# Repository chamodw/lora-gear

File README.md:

# lora-gear
Prototype application PCB for LoRA gear wearable activity tracker.

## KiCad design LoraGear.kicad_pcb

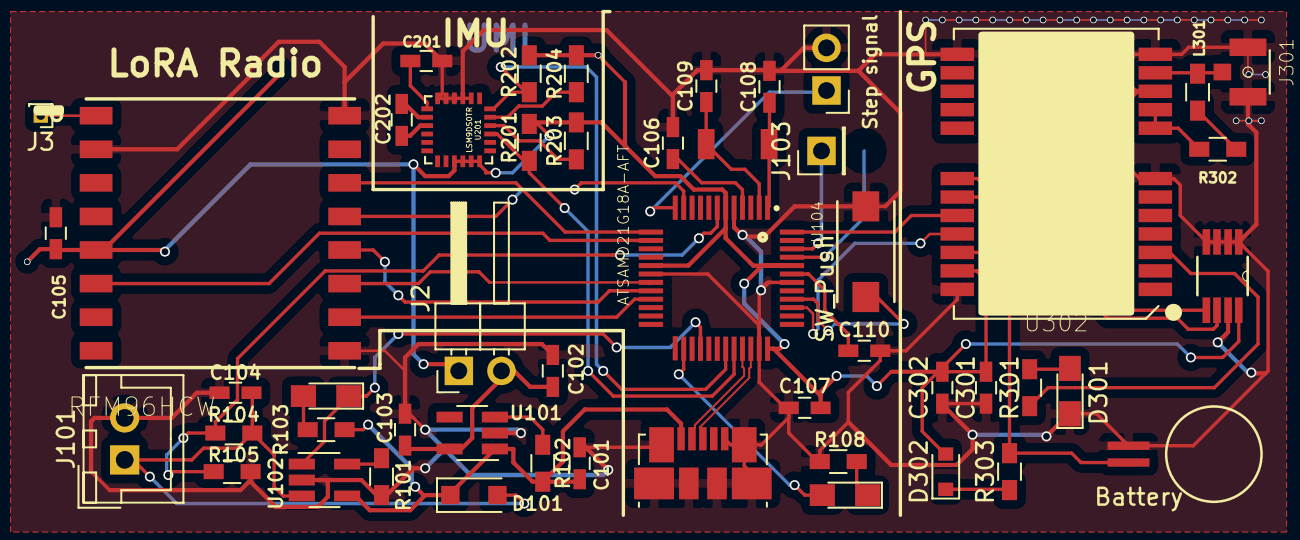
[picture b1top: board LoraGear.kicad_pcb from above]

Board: 2 copper layers, 50 parts (0 on the bottom side), 46 nets.

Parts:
BT301: Battery; MSBATT
C101, C102, C104, C105, C107, C201: 10uF; C_0603_HandSoldering
C103, C106, C110: 1uF; C_0603_HandSoldering
C108, C109: 22pf; C_0603_HandSoldering
C202: 0.22uF; C_0603_HandSoldering
C301: 10uf; C_0603_HandSoldering
C302: 0.1uF; C_0603_HandSoldering
D101: MBR120; D_SOD-123F
D102: CHARGE; LED_0805_HandSoldering
D105: LED; LED_0805_HandSoldering
D301: GPS; LED_0805_HandSoldering
D302: 5817; D_0805
J1: Step signal; Pin_Header_Straight_1x02_Pitch2.54mm
J2: I; Pin_Header_Angled_1x02_Pitch2.54mm
J3: Conn_01x01; Pin_Header_Straight_1x01_Pitch1.00mm
J101: BAT; JST_XH_B02B-XH-A_02x2.50mm_Straight
J102: USB_OTG; USB_Micro-B_Molex_47346-0001
J103: Conn_01x02_Male; Pin_Header_Straight_1x01_Pitch2.54mm
J301: U.FL-R-SMT-1(10); HRS_U.FL-R-SMT-1(10)
L301: 22uH; R_0603_HandSoldering
R101, R201, R202, R203, R204: 10k; R_0603_HandSoldering
R102, R104, R105: 100k; R_0603_HandSoldering
R103, R301, R303: 1k; R_0603_HandSoldering
R108: R; R_0603_HandSoldering
R302: 22R; R_0603_HandSoldering
SW101: SW_Push; tactile
U101: AP2112K-3.3; SOT-23-5_HandSoldering
U102: MCP73831T-2DCI/OT; SOT-23-5_HandSoldering
U103: RFM96HCW; XCVR_RFM95W-868S2
U104: ATSAMD21G18A-AFT; QFP50P900X900X120-48N
U201: LSM9DS0TR; LGA-24
U301: 24AA32A-I/MS; SOP65P490X110-8N
U302: MOUDLE-GPS-NEO-6M(24P-16X12.2MM); GPS24P-SMD-1.1-16X12.2MM
Y101: 32.768; RT321532.7686EXTTR

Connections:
+3V3: C105.1, C107.1, C301.1, C302.1, D302.2, J2.1, R201.1, R202.1, R203.1, R204.1, U103.5, U104.6, U104.17, U104.36, U104.44, U201.15, U201.16, U201.17, U201.18, U301.8, U302.23
+BATT: C104.1, D101.2, J101.1, R104.1, U102.3
/AREF: C106.1, U104.4
/BAT_LEVEL: R104.2, R105.1, U104.7
/CHG_STATUS: D102.1, U102.1, U104.28
/D3_IRQ: U103.6, U104.14
/D4_RST: U103.14, U104.13
/D8_CS: U103.13, U104.11
/D13: D105.2, U104.26
/D+: J102.3, U104.34
/D-: J102.2, U104.33
/GPS/ESCL: U301.6, U302.19
/GPS/ESDA: U301.5, U302.18
/GPS/GPS_ANT: J301.2, L301.2, U302.11
/LORA_ANT: J3.1, U103.1
/MISO: U103.10, U104.21
/MOSI: U103.11, U104.19
/REG_OUT: C102.1, C103.1, J2.2, U101.5
/RX: U104.48, U302.20
/SCK: U103.12, U104.20
/SCL: R201.2, U104.32, U201.21
/SDA: R202.2, U104.31, U201.24
/STEP_IN: J1.1, U104.12
/SWDIO: J103.1, U104.46
/TX: U104.39, U302.21
GNDD: BT301.2, C101.2, C102.2, C103.2, C104.2, C105.2, C106.2, C107.2, C108.2, C109.2, C110.2, C201.2, C301.2, C302.2, D301.1, J1.2, J101.2, J102.5, J102.6, J301.1, J301.3, R101.2, R105.2, R108.2, SW101.1, U101.2, U102.2, U103.2, U103.9, U103.16, U104.5, U104.18, U104.35, U104.42, U201.2, U201.3, U201.4, U201.5, U201.6, U301.1, U301.2, U301.3, U301.4, U301.7, U302.7, U302.10, U302.12, U302.13, U302.24
unnamed: BT301.1, R303.2, U302.22
unnamed: C108.1, U104.1, Y101.1
unnamed: C109.1, U104.2, Y101.2
unnamed: C110.1, U104.43
unnamed: C201.1, U201.7
unnamed: C202.1, U201.9
unnamed: C202.2, U201.8
unnamed: D102.2, R103.2
unnamed: D105.1, R108.1
unnamed: D301.2, R301.2
unnamed: D302.1, R303.1
unnamed: L301.1, R302.2
unnamed: R101.1, U102.5
unnamed: R102.2, U101.3
unnamed: R203.2, U201.22
unnamed: R204.2, U201.23
unnamed: R301.1, U302.3
unnamed: R302.1, U302.8, U302.9
unnamed: SW101.2, U104.40
VBUS: C101.1, D101.1, J102.1, R102.1, R103.1, U101.1, U102.4

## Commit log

2018-01-12 First board spin
